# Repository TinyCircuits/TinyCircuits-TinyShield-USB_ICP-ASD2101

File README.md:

# TinyCircuits TinyShield USB & ICP Board
# ASD2101 Rev6

The design files are located under design-files/ for the TinyCircuits ASD2101 Rev 6 PCB.  This is a TinyShield board (Square Version, 20mm x 20mm) that has a FTDI USB converter.

Format is in Cadsoft Eagle format - Eagle version 6.2 was used for the original design.

For more infomation on this, check out the product page at TinyCircuits.com:  https://tinycircuits.com/collections/communication/products/usb-tinyshield

# License:

Design by TinyCircuits.
All design files are released under the Creative Commons Attribution Share-Alike 3.0 License, see the following link for details: http://creativecommons.org/licenses/by-sa/3.0

All text above must be included in any redistribution or derived design

This project uses designs and concepts developed as part of the Arduino project and the LilyPad project.  The TinyCircuits design files themselves (schematics, PCB and libraries) are not directly derived from these works' design files and have been created new, however the concepts and basic architecture behind the TinyDuino and TinyLily products are derived and we thank the hard work of the organizations below for their contributions to open-source hardware:
  
Original Arduino Uno Design by Team Arduino

LilyPad Arduino Design by Leah Buechley and Sparkfun Electronics

Please support the open-source hardware community

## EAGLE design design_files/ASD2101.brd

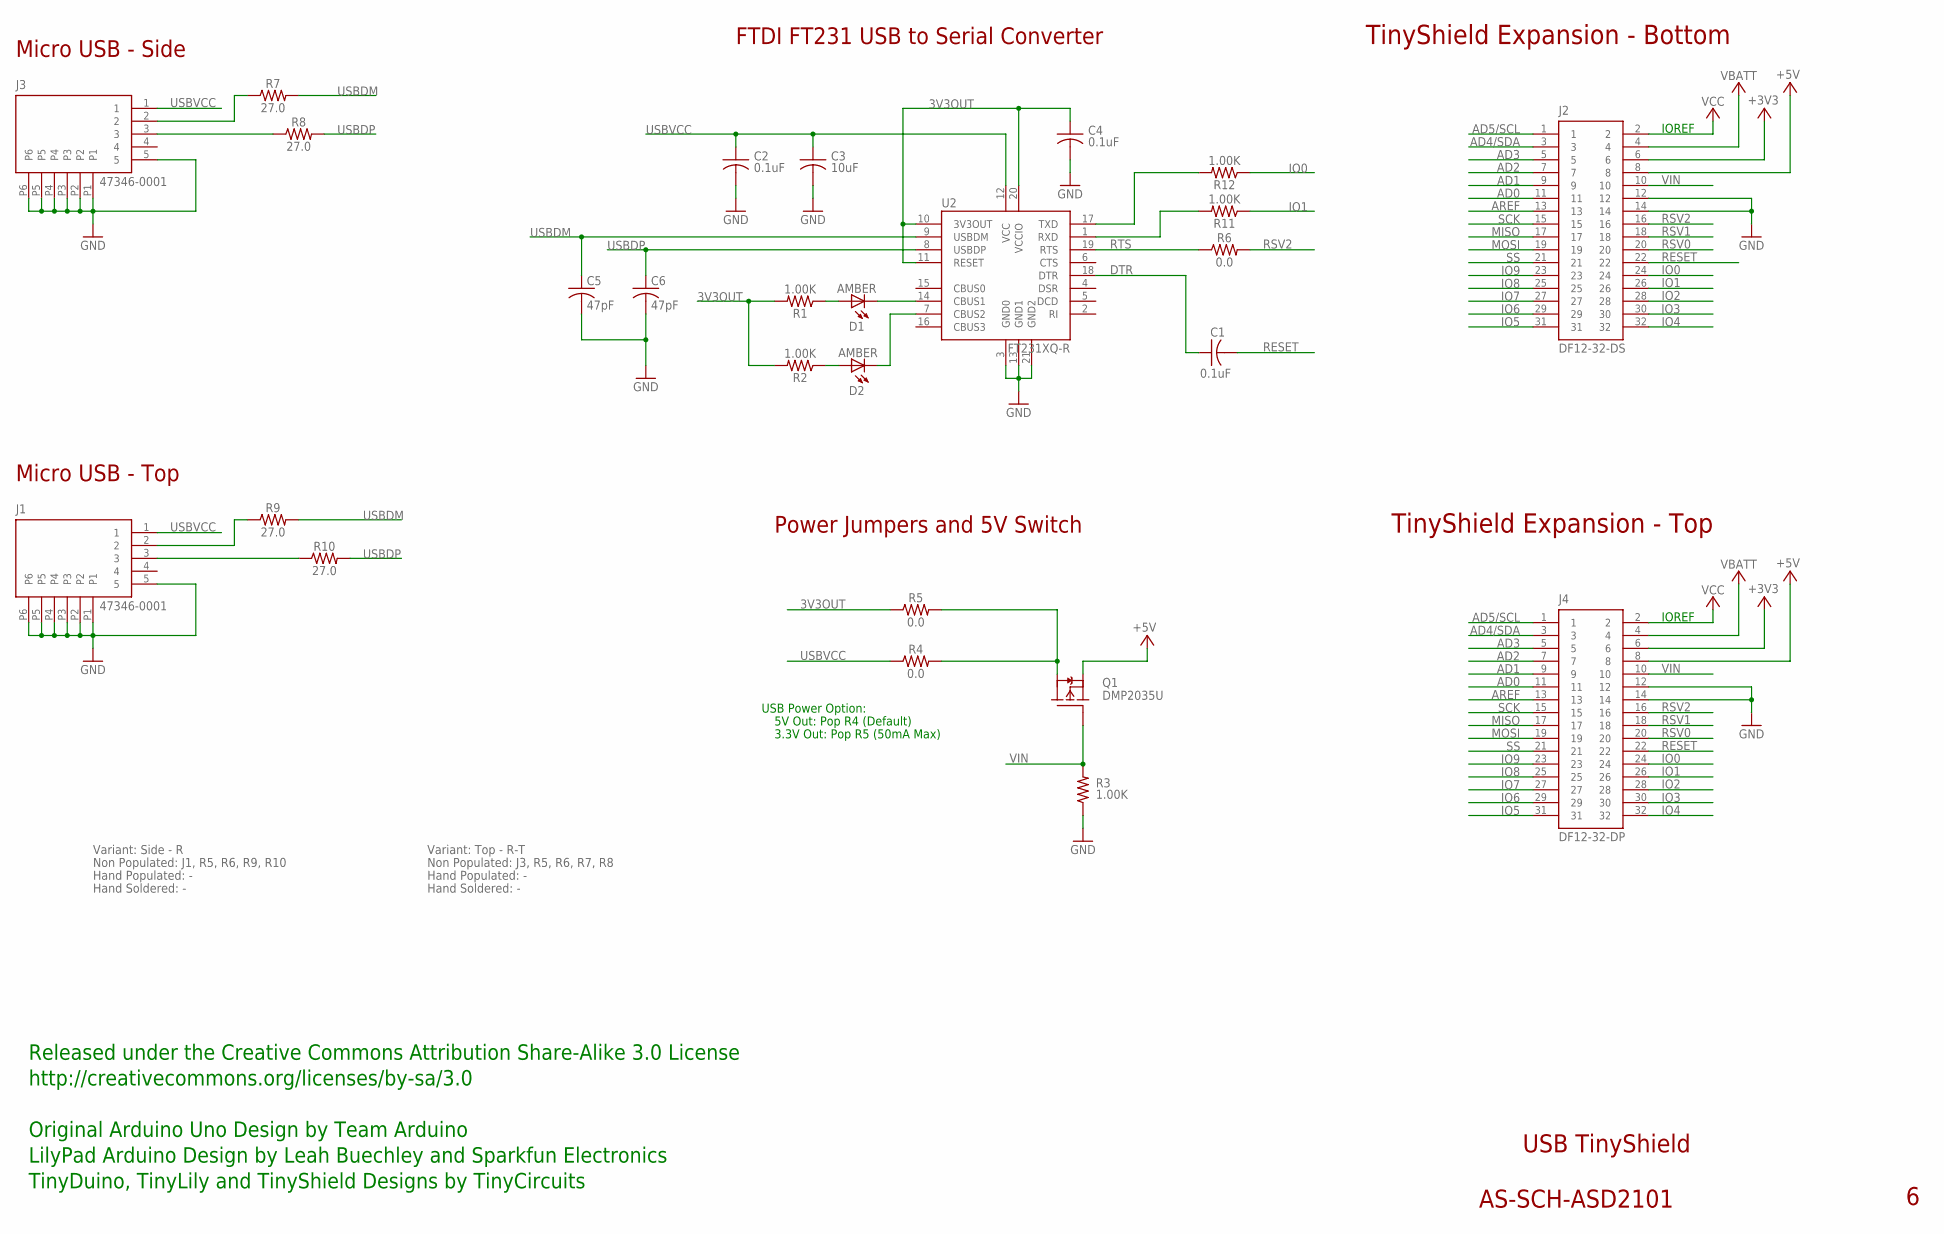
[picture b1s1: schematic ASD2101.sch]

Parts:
C1, C4: 0.1uF; C0402; PARTNO AS-ITM-00008
C2: 0.1uF; C0402
C3: 10uF; C0603
C5, C6: 47pF; 0402; PARTNO AS-ITM-00241
D1, D2: AMBER; LNJ_LED
J1, J3: 47346-0001; MICRO_USB; PARTNO AS-ITM-00021
J2: DF12-32-DS; PARTNO AS-ITM-00012
J4: DF12-32-DP; PARTNO AS-ITM-00015
Q1: DMP2035U; SOT23
R1, R2, R3: 1.00K; 0402
R4, R5: 0.0; 0402
R6: 0.0; 0402_SHORT
R7, R8, R9, R10: 27.0; 0402
R11, R12: 1.00K; 0402; PARTNO AS-ITM-00003
U2: FT231XQ-R; QFN20

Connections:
3V3OUT: C4.1, R1.2, R2.2, R5.1, U2.10 (3V3OUT), U2.11 (RESET), U2.20 (VCCIO)
+3V3: J2.6, J4.6
+5V: J2.8, J4.8, Q1.E (S)
AD0: J2.11, J4.11
AD1: J2.9, J4.9
AD2: J2.7, J4.7
AD3: J2.5, J4.5
AD4/SDA: J2.3, J4.3
AD5/SCL: J2.1, J4.1
AREF: J2.13, J4.13
DTR: C1.1, U2.18 (DTR)
GND: C2.2, C3.2, C4.2, C5.2, C6.2, J1.5, J1.P1, J1.P2, J1.P3, J1.P4, J1.P5, J1.P6, J2.12, J2.14, J3.5, J3.P1, J3.P2, J3.P3, J3.P4, J3.P5, J3.P6, J4.12, J4.14, R3.1, U2.3 (GND0), U2.13 (GND1), U2.21 (GND2)
IO0: J2.24, J4.24, R12.1
IO1: J2.26, J4.26, R11.1
IO2: J2.28, J4.28
IO3: J2.30, J4.30
IO4: J2.32, J4.32
IO5: J2.31, J4.31
IO6: J2.29, J4.29
IO7: J2.27, J4.27
IO8: J2.25, J4.25
IO9: J2.23, J4.23
MISO: J2.17, J4.17
MOSI: J2.19, J4.19
unnamed: J3.2, R7.1
unnamed: J1.2, R9.1
unnamed: J1.3, R10.1
unnamed: Q1.C (D), R4.2, R5.2
unnamed: D2.C, U2.7 (CBUS2)
unnamed: D1.A, R1.1
unnamed: D2.A, R2.1
unnamed: J3.3, R8.1
unnamed: R11.2, U2.1 (RXD)
unnamed: R12.2, U2.17 (TXD)
unnamed: D1.C, U2.14 (CBUS1)
RESET: C1.2, J2.22, J4.22
RSV0: J2.20, J4.20
RSV1: J2.18, J4.18
RSV2: J2.16, J4.16, R6.2
RTS: R6.1, U2.19 (RTS)
SCK: J2.15, J4.15
SS: J2.21, J4.21
USBDM: C5.1, R7.2, R9.2, U2.9 (USBDM)
USBDP: C6.1, R8.2, R10.2, U2.8 (USBDP)
USBVCC: C2.1, C3.1, J1.1, J3.1, R4.1, U2.12 (VCC)
VBATT: J2.4, J4.4
VCC: J2.2, J4.2
VIN: J2.10, J4.10, Q1.B (G), R3.2

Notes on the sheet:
TinyShield Expansion - Bottom
USB TinyShield
AS-SCH-ASD2101
TinyShield Expansion - Top
IOREF
Micro USB - Side
Released under the Creative Commons Attribution Share-Alike 3.0 License
http://creativecommons.org/licenses/by-sa/3.0
Original Arduino Uno Design by Team Arduino
TinyDuino, TinyLily and TinyShield Designs by TinyCircuits
LilyPad Arduino Design by Leah Buechley and Sparkfun Electronics
USB Power Option:
5V Out: Pop R4 (Default)
3.3V Out: Pop R5 (50mA Max)
Micro USB - Top
FTDI FT231 USB to Serial Converter
Power Jumpers and 5V Switch
Non Populated: J1, R5, R6, R9, R10
Hand Populated: -
Hand Soldered: -
Variant: Side - R
Non Populated: J3, R5, R6, R7, R8
Variant: Top - R-T

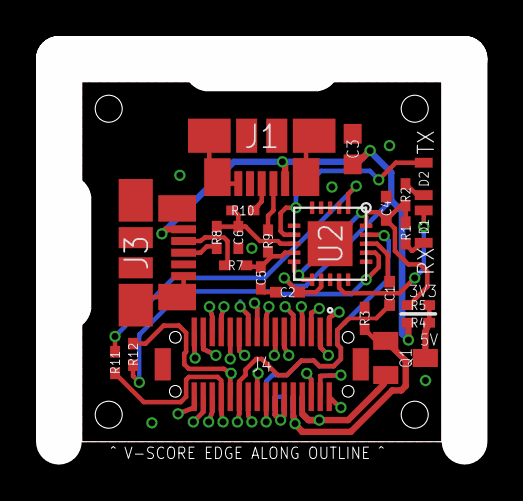
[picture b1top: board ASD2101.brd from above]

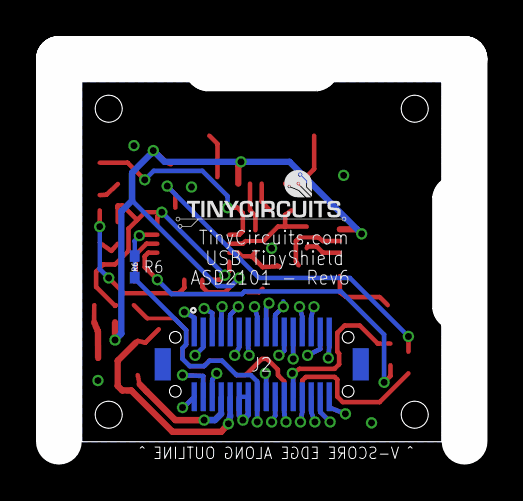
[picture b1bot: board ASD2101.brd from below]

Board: 2 copper layers, 20.0 x 20.0 mm, 27 parts (2 on the bottom side), 48 nets.

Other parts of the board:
U$1: DOCFIELD-TINYCIRCUITS-PCB

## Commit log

2013-06-30 Updated project link
2013-12-22 Updated to Rev4
2014-08-24 Updated Link
2015-02-22 Updated to Rev 6
2015-02-22 Update typo
2019-01-02 update format
2020-07-28 Add CAD data
2020-08-14 Update CAD drawing
